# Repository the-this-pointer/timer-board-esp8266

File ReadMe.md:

#### Timer Board

This project contains design files and software of a modular digital timer supporting wifi / gsm communication.

External component libraries located [here](https://github.com/the-this-pointer/kicad-my-libraries)

###### TODO:

- Power Module
- GSM Module
- Firmware for new PCB

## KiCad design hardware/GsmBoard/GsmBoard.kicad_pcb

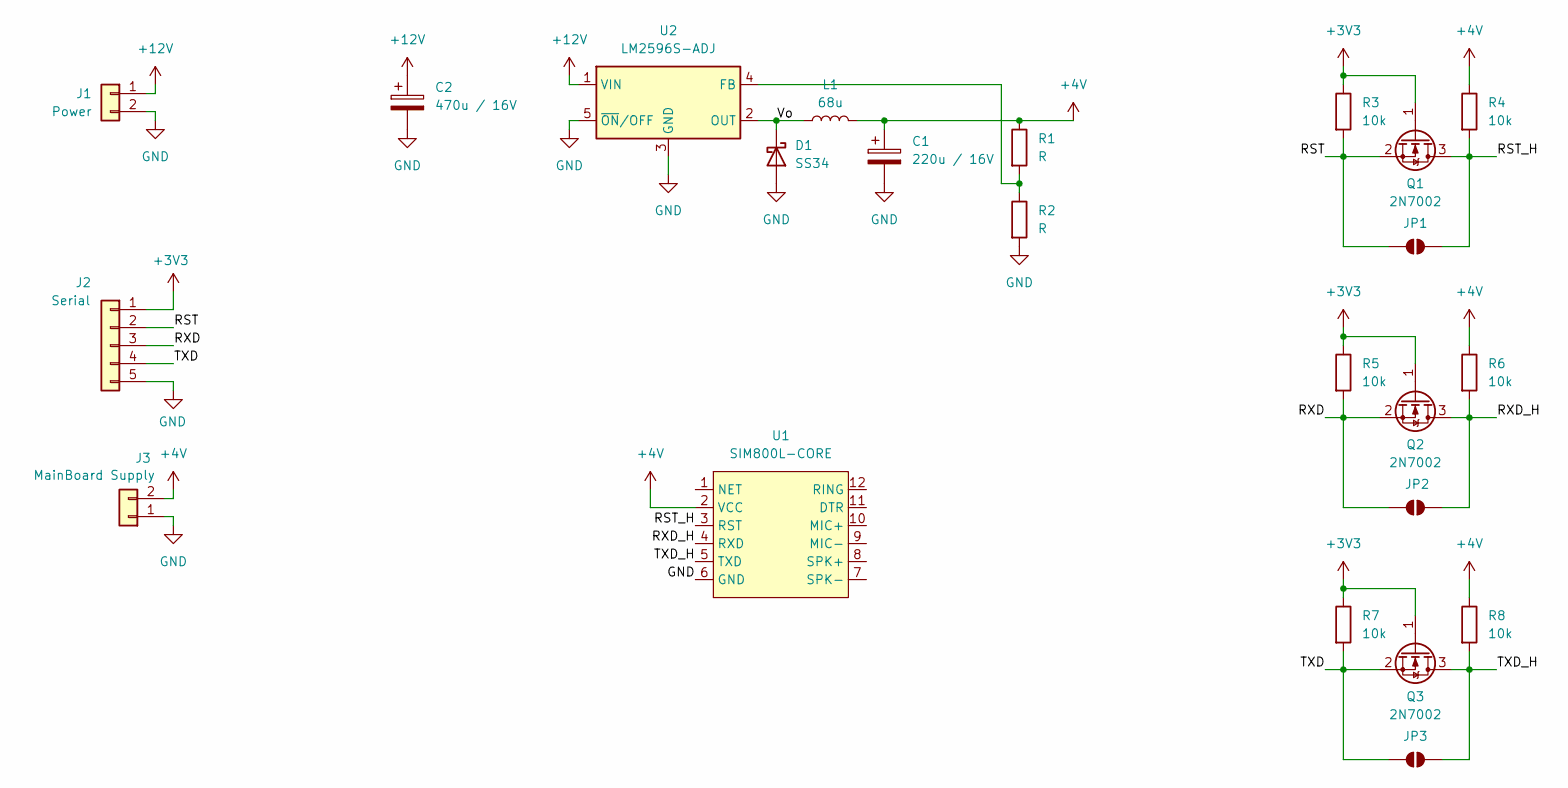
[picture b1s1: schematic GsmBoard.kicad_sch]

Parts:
C1: 220u / 16V; CP_Elec_6.3x7.7
C2: 470u / 16V; CP_Elec_8x10
D1: SS34; D_SMA
J1: Power; JST_VH_B2P-VH_1x02_P3.96mm_Vertical
J2: Serial; JST_XH_B5B-XH-A_1x05_P2.50mm_Vertical
J3: MainBoard Supply; JST_XH_B2B-XH-A_1x02_P2.50mm_Vertical
JP1, JP2, JP3: SolderJumper_2_Open; SolderJumper-2_P1.3mm_Open_RoundedPad1.0x1.5mm
L1: 68u; L_12x12mm_H8mm
Q1, Q2, Q3: 2N7002; SOT-23_Handsoldering
R1, R2: R; R_1206_3216Metric_Pad1.30x1.75mm_HandSolder
R3, R4, R5, R6, R7, R8: 10k; R_1206_3216Metric_Pad1.30x1.75mm_HandSolder
U1: SIM800L-CORE
U2: LM2596S-ADJ; TO-263-5_TabPin3

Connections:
+3V3: J2.1, Q1.1 (G), Q2.1 (G), Q3.1 (G), R3.1, R5.1, R7.1
+4V: C1.1, J3.2, L1.2, R1.1, R4.1, R6.1, R8.1, U1.2 (VCC)
+12V: C2.1, J1.1, U2.1 (VIN)
/RST: J2.2, JP1.1 (A), Q1.2 (S), R3.2
/RST_H: JP1.2 (B), Q1.3 (D), R4.2, U1.3 (RST)
/RXD: J2.3, JP2.1 (A), Q2.2 (S), R5.2
/RXD_H: JP2.2 (B), Q2.3 (D), R6.2, U1.4 (RXD)
/TXD: J2.4, JP3.1 (A), Q3.2 (S), R7.2
/TXD_H: JP3.2 (B), Q3.3 (D), R8.2, U1.5 (TXD)
/Vo: D1.1 (K), L1.1, U2.2 (OUT)
GND: C1.2, C2.2, D1.2 (A), J1.2, J2.5, J3.1, R2.2, U1.6 (GND), U2.3 (GND), U2.5 (~ON/OFF)
unnamed: R1.2, R2.1, U2.4 (FB)

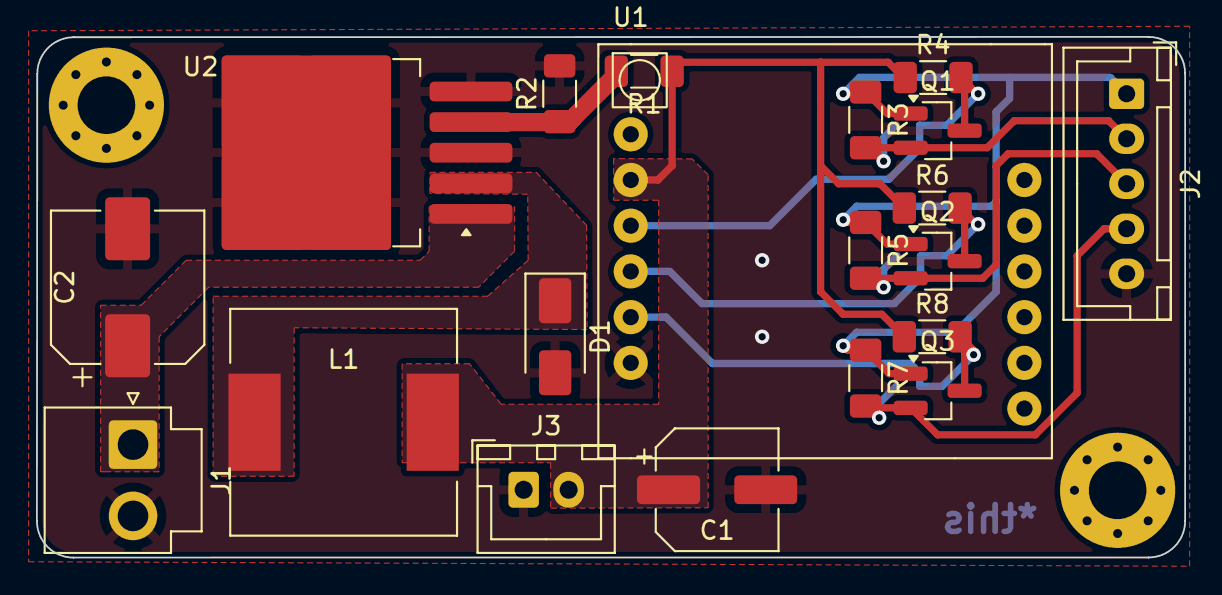
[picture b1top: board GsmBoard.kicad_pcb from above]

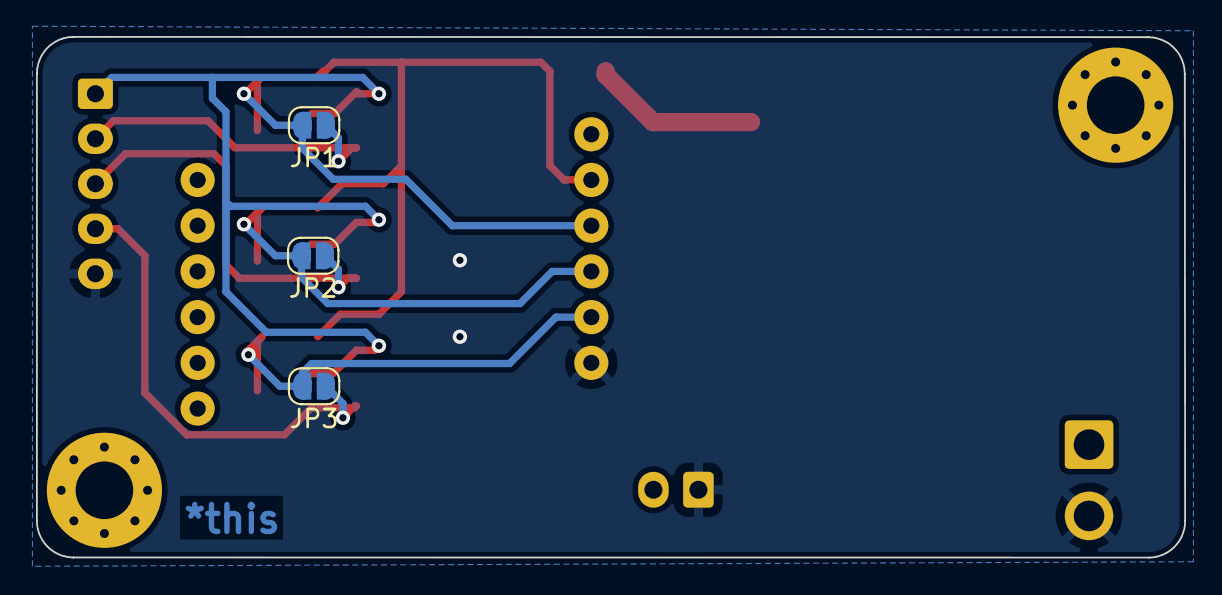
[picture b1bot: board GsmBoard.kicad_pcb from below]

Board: 2 copper layers, 63.8 x 28.9 mm, 23 parts (3 on the bottom side), 12 nets.

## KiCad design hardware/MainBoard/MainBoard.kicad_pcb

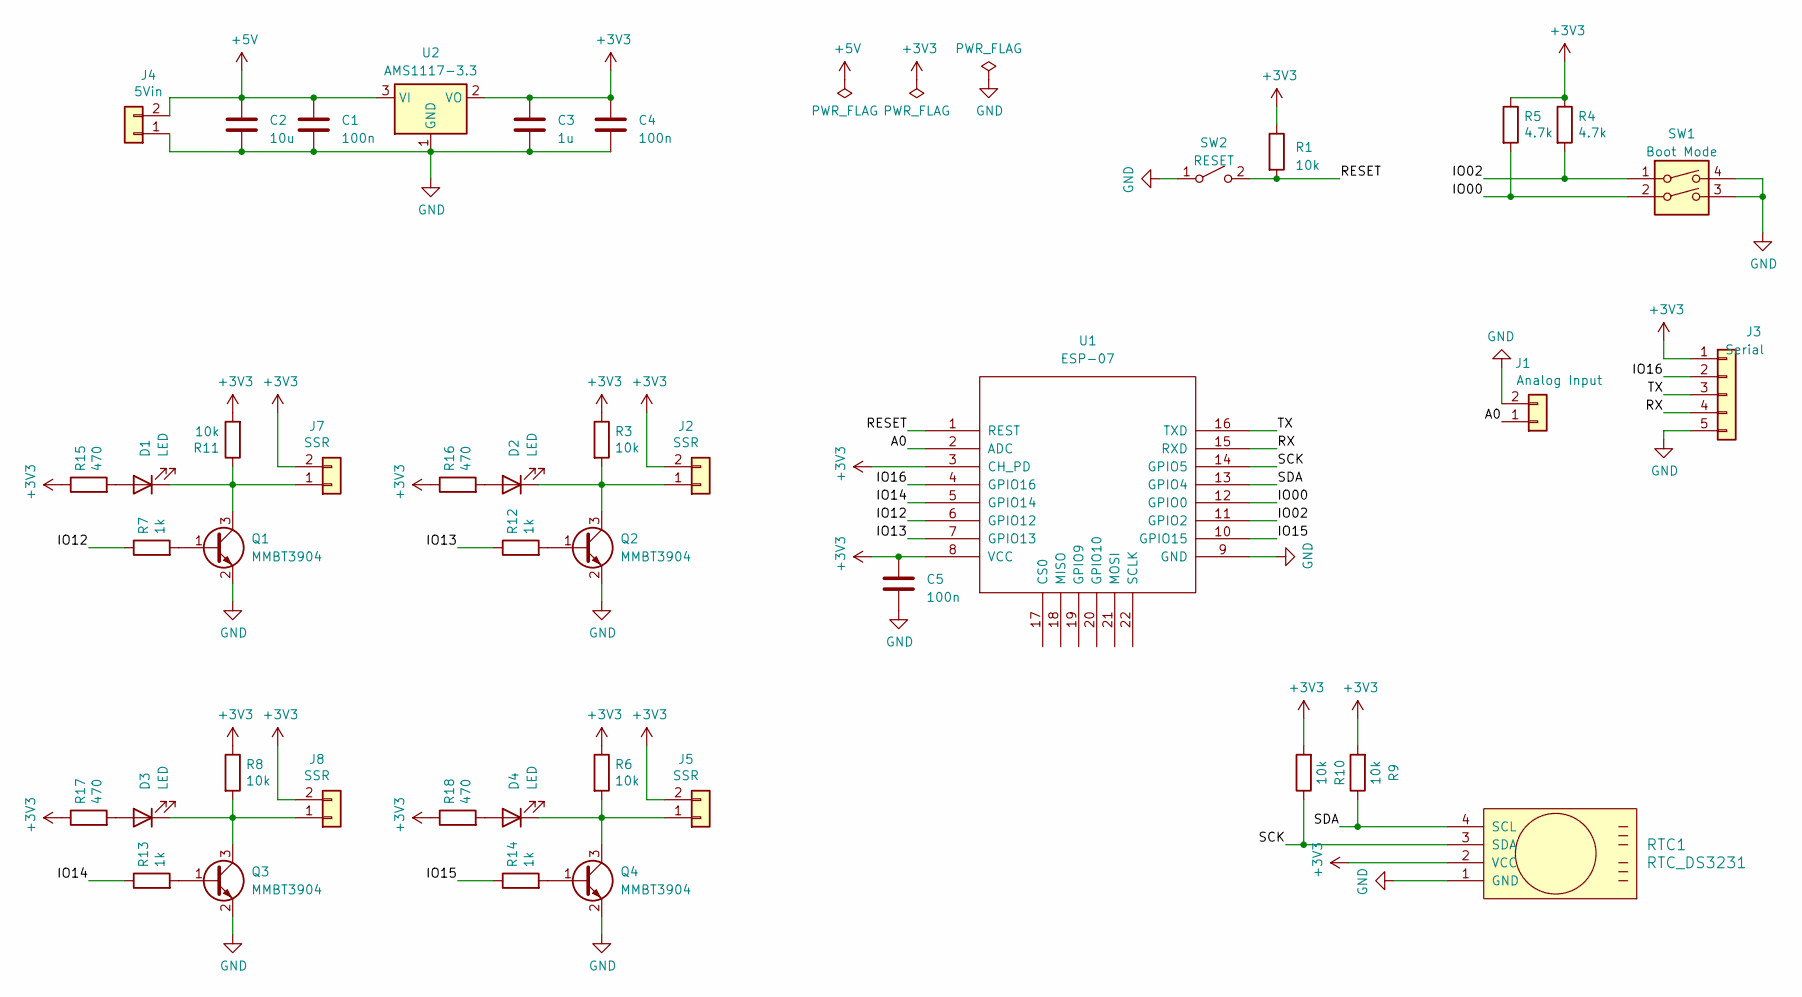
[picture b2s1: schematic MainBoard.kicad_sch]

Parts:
C1, C4, C5: 100n; C_1206_3216Metric_Pad1.33x1.80mm_HandSolder
C2: 10u; C_1206_3216Metric_Pad1.33x1.80mm_HandSolder
C3: 1u; C_1206_3216Metric_Pad1.33x1.80mm_HandSolder
D1, D2, D3, D4: LED; LED_1206_3216Metric_Pad1.42x1.75mm_HandSolder
J1: Analog Input; JST_XH_B2B-XH-A_1x02_P2.50mm_Vertical
J2, J5, J7, J8: SSR; JST_XH_B2B-XH-A_1x02_P2.50mm_Vertical
J3: Serial; JST_XH_B5B-XH-A_1x05_P2.50mm_Vertical
J4: 5Vin; JST_XH_B2B-XH-A_1x02_P2.50mm_Vertical
Q1, Q2, Q3, Q4: MMBT3904; SOT-23
R1, R3, R6, R8, R9, R10, R11: 10k; R_1206_3216Metric_Pad1.30x1.75mm_HandSolder
R4, R5: 4.7k; R_1206_3216Metric_Pad1.30x1.75mm_HandSolder
R7, R12, R13, R14: 1k; R_1206_3216Metric_Pad1.30x1.75mm_HandSolder
R15, R16, R17, R18: 470; R_1206_3216Metric_Pad1.30x1.75mm_HandSolder
RTC1: RTC_DS3231
SW1: Boot Mode; SW_DIP_SPSTx02_Slide_9.78x7.26mm_W7.62mm_P2.54mm
SW2: RESET; SW_SPST_FSMSM
U1: ESP-07; ESP-07-RF_Modules
U2: AMS1117-3.3; SOT-223-3_TabPin2

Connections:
+3V3: C3.1, C4.1, C5.1, J2.2, J3.1, J5.2, J7.2, J8.2, R1.1, R3.1, R4.1, R5.1, R6.1, R8.1, R9.2, R10.2, R11.2, R15.1, R16.1, R17.1, R18.1, RTC1.2 (VCC), U1.3 (CH_PD), U1.8 (VCC), U2.2 (VO)
+5V: C1.1, C2.1, J4.2, U2.3 (VI)
/A0: J1.1, U1.2 (ADC)
/IO00: R5.2, SW1.2, U1.12 (GPIO0)
/IO02: R4.2, SW1.1, U1.11 (GPIO2)
/IO12: R7.1, U1.6 (GPIO12)
/IO13: R12.1, U1.7 (GPIO13)
/IO14: R13.1, U1.5 (GPIO14)
/IO15: R14.1, U1.10 (GPIO15)
/IO16: J3.2, U1.4 (GPIO16)
/RESET: R1.2, SW2.2 (B), U1.1 (REST)
/RX: J3.4, U1.15 (RXD)
/SCK: R10.1, RTC1.3 (SDA), U1.14 (GPIO5)
/SDA: R9.1, RTC1.4 (SCL), U1.13 (GPIO4)
/TX: J3.3, U1.16 (TXD)
GND: C1.2, C2.2, C3.2, C4.2, C5.2, J1.2, J3.5, J4.1, Q1.2 (E), Q2.2 (E), Q3.2 (E), Q4.2 (E), RTC1.1 (GND), SW1.3, SW1.4, SW2.1 (A), U1.9 (GND), U2.1 (GND)
unnamed: D1.2 (A), R15.2
unnamed: D1.1 (K), J7.1, Q1.3 (C), R11.1
unnamed: D2.2 (A), R16.2
unnamed: D2.1 (K), J2.1, Q2.3 (C), R3.2
unnamed: D3.2 (A), R17.2
unnamed: D3.1 (K), J8.1, Q3.3 (C), R8.2
unnamed: D4.2 (A), R18.2
unnamed: D4.1 (K), J5.1, Q4.3 (C), R6.2
unnamed: Q1.1 (B), R7.2
unnamed: Q2.1 (B), R12.2
unnamed: Q3.1 (B), R13.2
unnamed: Q4.1 (B), R14.2

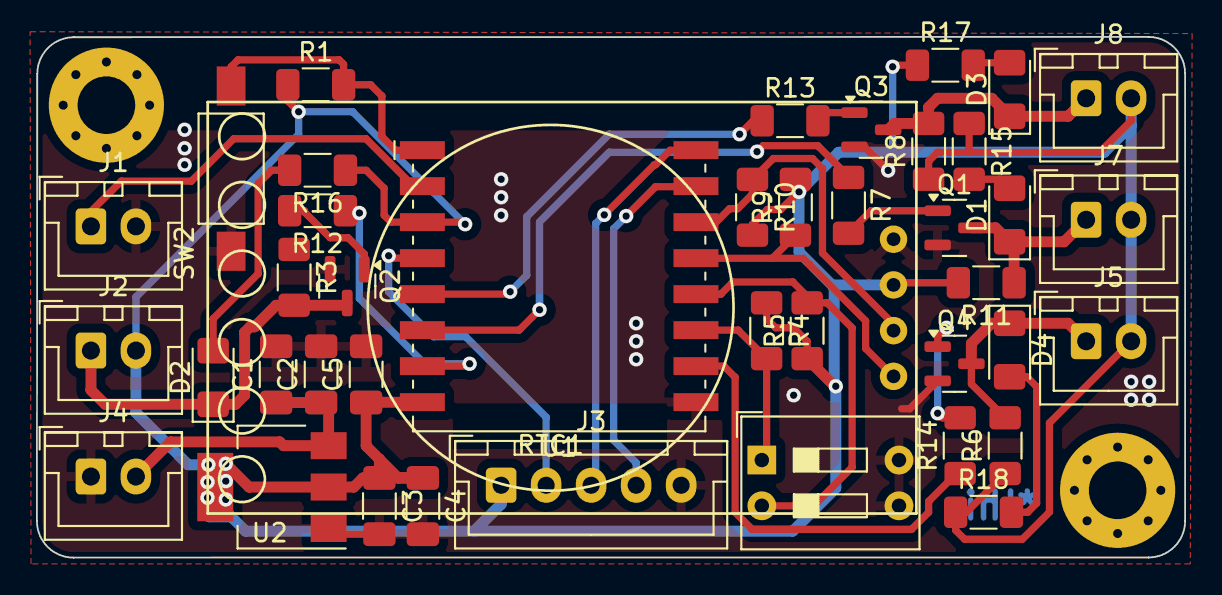
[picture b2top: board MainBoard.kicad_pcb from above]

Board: 2 copper layers, 63.8 x 28.9 mm, 42 parts (0 on the bottom side), 28 nets.

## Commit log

2024-05-24 led indicators added to outputs
2024-05-28 Template files added
2024-05-30 gsm board module designed
2024-05-31 main board power connector added to module
